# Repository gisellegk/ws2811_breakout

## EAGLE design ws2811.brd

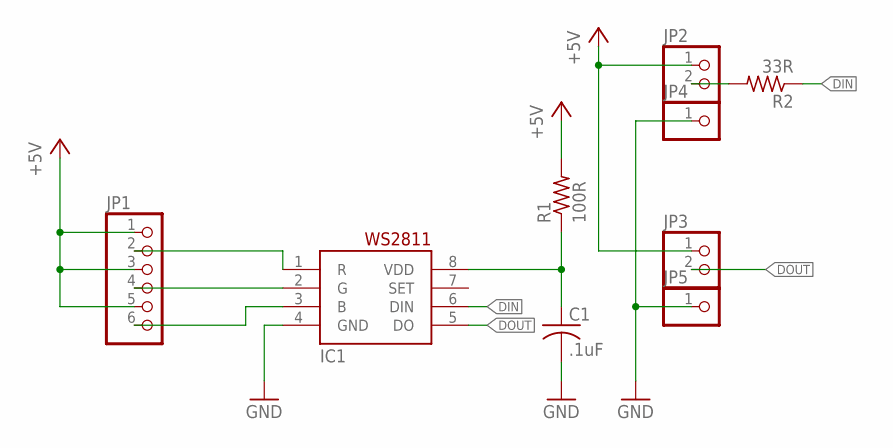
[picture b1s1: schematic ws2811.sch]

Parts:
C1: .1uF; C0402
IC1: WS2811-SOP8; SO08-SKINNYPADS
JP1: PINHD-1X6; 1X06
JP2, JP3: PINHD-1X2; 1X02
JP4, JP5: PINHD-1X1; 1X01
R1: 100R; R0402
R2: 33R; R0402

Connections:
+5V: JP1.1, JP1.3, JP1.5, JP2.1, JP3.1, R1.2
DIN: IC1.6 (DIN), R2.1
DOUT: IC1.5 (DO), JP3.2
GND: C1.2, IC1.4 (GND), JP4.1, JP5.1
unnamed: C1.1, IC1.8 (VDD), R1.1
unnamed: JP2.2, R2.2
unnamed: IC1.1 (R), JP1.2
unnamed: IC1.2 (G), JP1.4
unnamed: IC1.3 (B), JP1.6

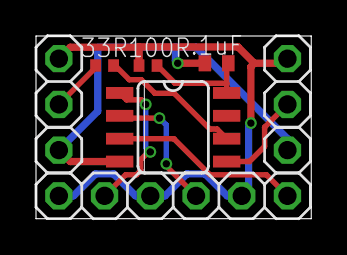
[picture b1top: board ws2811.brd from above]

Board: 2 copper layers, 15.3 x 10.2 mm, 9 parts (0 on the bottom side), 9 nets.
